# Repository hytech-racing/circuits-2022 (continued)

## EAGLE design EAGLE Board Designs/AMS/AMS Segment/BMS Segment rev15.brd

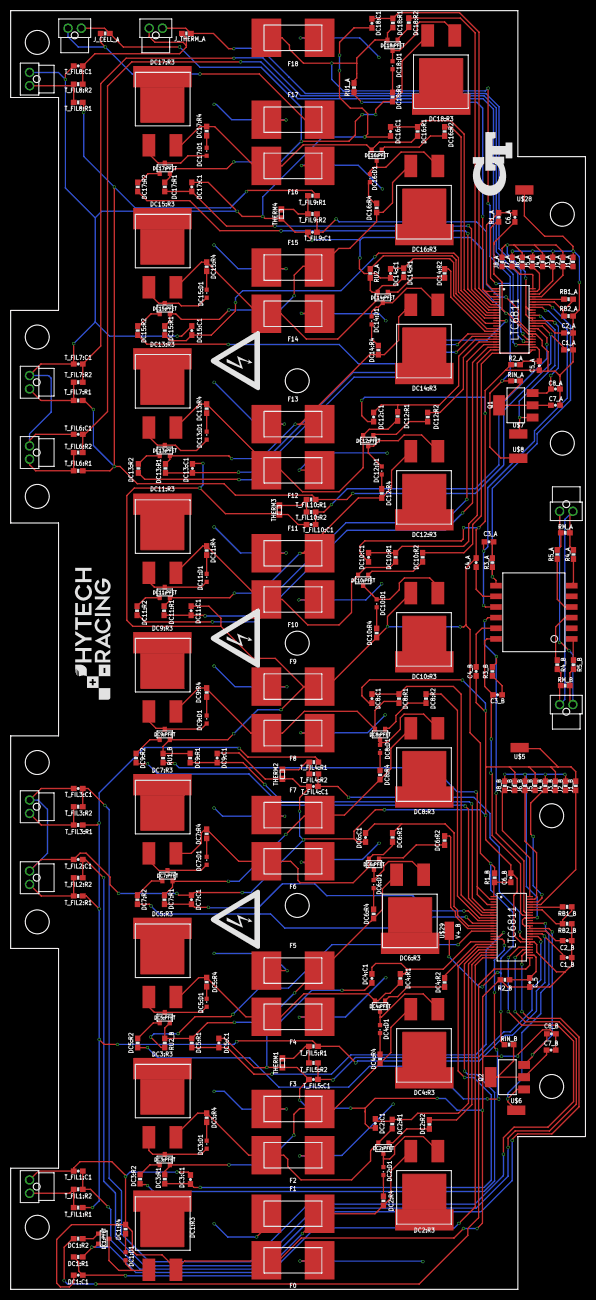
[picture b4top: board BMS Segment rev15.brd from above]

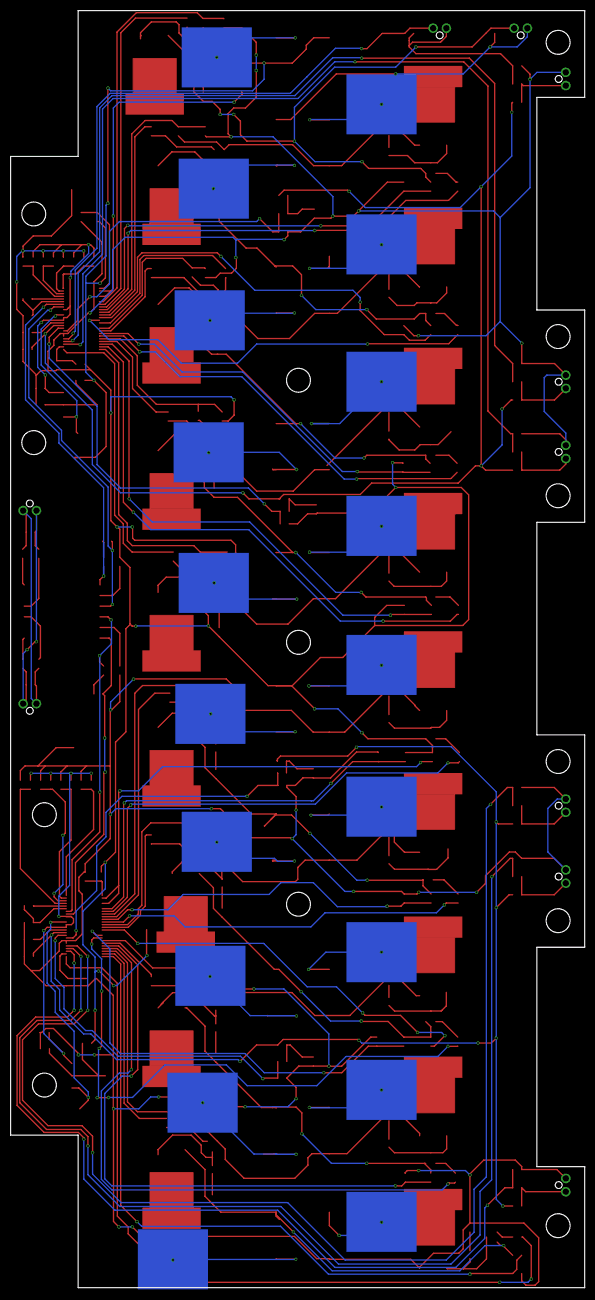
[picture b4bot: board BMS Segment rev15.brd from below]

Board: 2 copper layers, 108.0 x 240.3 mm, 294 parts (19 on the bottom side), 194 nets.

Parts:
AMS_CELL_TEST: AMS_CELL_TEST; NANO-FIT_VERTICAL-2
AMS_THERM_TEST: AMS_THERM_TEST; NANO-FIT_VERTICAL-2
C1_A, C1_B, C2_A, C2_B, C8_A, C8_B: 1uF; 0603-CAP
C3_A, C3_B: 15pF; 0603-CAP
C4_A, C4_B, C5_A: 10nF; 0603-CAP
C6_A, C6_B, C7_A, C7_B: 100nF; 0603-CAP
CELL0, CELL1, CELL2, CELL3, CELL4, CELL5, CELL6, CELL7, CELL8, CELL9, CELL10, CELL11, CELL12, CELL13, CELL14, CELL15, CELL16, CELL17, CELL18: BATTERY_SPRING_KEYSTONE5222; KEYSTONE5222
C_5: 10nF; 0603-CAP
DC1:C1, DC2:C1, DC3:C1, DC4:C1, DC5:C1, DC6:C1, DC7:C1, DC8:C1, DC9:C1, DC10:C1, DC11:C1, DC12:C1, DC13:C1, DC14:C1, DC15:C1, DC16:C1, DC17:C1, DC18:C1: 10nF; 0603-CAP
DC1:D1, DC2:D1, DC3:D1, DC4:D1, DC5:D1, DC6:D1, DC7:D1, DC8:D1, DC9:D1, DC10:D1, DC11:D1, DC12:D1, DC13:D1, DC14:D1, DC15:D1, DC16:D1, DC17:D1, DC18:D1: RED; LED-603
DC1:PFET, DC2:PFET, DC3:PFET, DC4:PFET, DC5:PFET, DC6:PFET, DC7:PFET, DC8:PFET, DC9:PFET, DC10:PFET, DC11:PFET, DC12:PFET, DC13:PFET, DC14:PFET, DC15:PFET, DC16:PFET, DC17:PFET, DC18:PFET: P-CHANNEL_MOSFET_DMP3099L-7; SOT23
DC1:R1, DC2:R1, DC3:R1, DC4:R1, DC5:R1, DC6:R1, DC7:R1, DC8:R1, DC9:R1, DC10:R1, DC11:R1, DC12:R1, DC13:R1, DC14:R1, DC15:R1, DC16:R1, DC17:R1, DC18:R1: 100R; 0603-RES@1
DC1:R2, DC2:R2, DC3:R2, DC4:R2, DC5:R2, DC6:R2, DC7:R2, DC8:R2, DC9:R2, DC10:R2, DC11:R2, DC12:R2, DC13:R2, DC14:R2, DC15:R2, DC16:R2, DC17:R2, DC18:R2: 3K3; 0603-RES@1
DC1:R3, DC2:R3, DC3:R3, DC4:R3, DC5:R3, DC6:R3, DC7:R3, DC8:R3, DC9:R3, DC10:R3, DC11:R3, DC12:R3, DC13:R3, DC14:R3, DC15:R3, DC16:R3, DC17:R3, DC18:R3: RESISTOR_PWR263_; PWR263
DC1:R4, DC2:R4, DC3:R4, DC4:R4, DC5:R4, DC6:R4, DC7:R4, DC8:R4, DC9:R4, DC10:R4, DC11:R4, DC12:R4, DC13:R4, DC14:R4, DC15:R4, DC16:R4, DC17:R4, DC18:R4: 806R; 0603-RES@1
F0, F1, F2, F3, F4, F5, F6, F7, F8, F9, F10, F11, F12, F13, F14, F15, F16, F17, F18: 0001.2704.11; 0885
ISOSPI_A: ISOSPI; NANO-FIT_VERTICAL-2
ISOSPI_B: ISOSPI; NANO-FIT_VERTICAL-2
J1_A, J1_B, J2_A, J2_B, J3_A, J3_B, J4_A, J4_B, J5_A, J5_B, J6_A, J6_B, J7_A, J7_B, J8_A, J8_B: 0R; 0603-RES@1
J_CELL_A: 0R; 0603-RES@1
J_THERM_A: 0R; 0603-RES@1
Q1, Q2: NSV1C201MZ4; SOT223
R1_A, R1_B, R2_A, R2_B: 100R; 0603-RES@1
R3_A, R3_B: 402R; 0603-RES@1
R4_A, R4_B, R5_A, R5_B: 22R; 0603-RES@1
RB1_A, RB1_B: 1K2; 0603-RES@1
RB2_A, RB2_B: 806R; 0603-RES@1
RIN_A: 100R; 0603-RES@1
RIN_B: 100R; 0603-RES@1
RM_A: 100R; 0603-RES@1
RM_B: 100R; 0603-RES@1
RU1_A, RU1_B, RU2_A, RU2_B: 100R; 0603-RES@1
THERM1, THERM2, THERM3, THERM4: 10K; 0603
THERM1_A, THERM1_B, THERM2_A, THERM2_B, THERM3_A, THERM3_B: THERMISTOR; NANO-FIT_VERTICAL-2
TRANSFORMER: HM2102NLT
T_FIL1:C1, T_FIL2:C1, T_FIL3:C1, T_FIL4:C1, T_FIL5:C1, T_FIL6:C1, T_FIL7:C1, T_FIL8:C1, T_FIL9:C1, T_FIL10:C1: 10nF; 0603-CAP
T_FIL1:R1, T_FIL2:R1, T_FIL3:R1, T_FIL4:R1, T_FIL5:R1, T_FIL6:R1, T_FIL7:R1, T_FIL8:R1, T_FIL9:R1, T_FIL10:R1: 10K; 0603-RES@1
T_FIL1:R2, T_FIL2:R2, T_FIL3:R2, T_FIL4:R2, T_FIL5:R2, T_FIL6:R2, T_FIL7:R2, T_FIL8:R2, T_FIL9:R2, T_FIL10:R2: 100R; 0603-RES@1
U1, U2: LTC6811-2; LTC6811
U$1: LOGO_HYTECH_1.0"
U$2: LOGO_GT_0.50"
U$3, U$4, U$20: HV_1.00"
U$5, U$6, U$7, U$8, U$28, U$29: TEST_POINTMICRO_MINIATURE; MICRO_MINIATURE
U$9, U$10, U$11, U$12, U$13, U$14, U$15, U$16, U$17, U$18, U$19, U$26, U$27: M4_MOUNTING
U$21: NUMBER

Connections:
C0_A: C5_A.1, R2_A.2, U1.26
C0_B: C_5.1, R2_B.2, U2.26
C1_A: DC10:C1.1, DC10:R1.2, U1.24
C1_B: DC1:C1.1, DC1:R1.2, U2.24
C2_A: DC11:C1.1, DC11:R1.2, U1.22
C2_B: DC2:C1.1, DC2:R1.2, U2.22
C3_A: DC12:C1.1, DC12:R1.2, U1.20
C3_B: DC3:C1.1, DC3:R1.2, U2.20
C4_A: DC13:C1.1, DC13:R1.2, U1.18
C4_B: DC4:C1.1, DC4:R1.2, U2.18
C5_A: DC14:C1.1, DC14:R1.2, U1.16
C5_B: DC5:C1.1, DC5:R1.2, U2.16
C7_A: DC15:C1.1, DC15:R1.2, U1.12
C7_B: DC6:C1.1, DC6:R1.2, U2.12
C8_A: DC16:C1.1, DC16:R1.2, U1.10
C8_B: DC7:C1.1, DC7:R1.2, U2.10
C9_A: DC17:C1.1, DC17:R1.2, U1.8
C9_B: DC8:C1.1, DC8:R1.2, U2.8
C10_A: DC18:C1.1, DC18:R1.2, U1.6
C10_B: DC9:C1.1, DC9:R1.2, U2.6
CC0: CELL0.1, F0.1
CC1: CELL1.1, F1.1
CC2: CELL2.1, F2.1
CC3: CELL3.1, F3.1
CC4: CELL4.1, F4.1
CC5: CELL5.1, F5.1
CC6: CELL6.1, F6.1
CC7: CELL7.1, F7.1
CC8: CELL8.1, F8.1
CC9: CELL9.1, F9.1
CC10: CELL10.1, F10.1
CC11: CELL11.1, F11.1
CC12: CELL12.1, F12.1
CC13: CELL13.1, F13.1
CC14: CELL14.1, F14.1
CC15: CELL15.1, F15.1
CC16: CELL16.1, F16.1
CC17: CELL17.1, F17.1
CC18: CELL18.1, F18.1
DC1:GATE: DC1:PFET.1, DC1:R2.1
DC1:N$1: DC1:D1.A, DC1:PFET.3, DC1:R3.1
DC1:N$2: DC1:D1.C, DC1:R4.2
DC2:GATE: DC2:PFET.1, DC2:R2.1
DC2:N$1: DC2:D1.A, DC2:PFET.3, DC2:R3.1
DC2:N$2: DC2:D1.C, DC2:R4.2
DC3:GATE: DC3:PFET.1, DC3:R2.1
DC3:N$1: DC3:D1.A, DC3:PFET.3, DC3:R3.1
DC3:N$2: DC3:D1.C, DC3:R4.2
DC4:GATE: DC4:PFET.1, DC4:R2.1
DC4:N$1: DC4:D1.A, DC4:PFET.3, DC4:R3.1
DC4:N$2: DC4:D1.C, DC4:R4.2
DC5:GATE: DC5:PFET.1, DC5:R2.1
DC5:N$1: DC5:D1.A, DC5:PFET.3, DC5:R3.1
DC5:N$2: DC5:D1.C, DC5:R4.2
DC6:GATE: DC6:PFET.1, DC6:R2.1
DC6:N$1: DC6:D1.A, DC6:PFET.3, DC6:R3.1
DC6:N$2: DC6:D1.C, DC6:R4.2
DC7:GATE: DC7:PFET.1, DC7:R2.1
DC7:N$1: DC7:D1.A, DC7:PFET.3, DC7:R3.1
DC7:N$2: DC7:D1.C, DC7:R4.2
DC8:GATE: DC8:PFET.1, DC8:R2.1
DC8:N$1: DC8:D1.A, DC8:PFET.3, DC8:R3.1
DC8:N$2: DC8:D1.C, DC8:R4.2
DC9:GATE: DC9:PFET.1, DC9:R2.1
DC9:N$1: DC9:D1.A, DC9:PFET.3, DC9:R3.1
DC9:N$2: DC9:D1.C, DC9:R4.2
DC10:GATE: DC10:PFET.1, DC10:R2.1
DC10:N$1: DC10:D1.A, DC10:PFET.3, DC10:R3.1
DC10:N$2: DC10:D1.C, DC10:R4.2
DC11:GATE: DC11:PFET.1, DC11:R2.1
DC11:N$1: DC11:D1.A, DC11:PFET.3, DC11:R3.1
DC11:N$2: DC11:D1.C, DC11:R4.2
DC12:GATE: DC12:PFET.1, DC12:R2.1
DC12:N$1: DC12:D1.A, DC12:PFET.3, DC12:R3.1
DC12:N$2: DC12:D1.C, DC12:R4.2
DC13:GATE: DC13:PFET.1, DC13:R2.1
DC13:N$1: DC13:D1.A, DC13:PFET.3, DC13:R3.1
DC13:N$2: DC13:D1.C, DC13:R4.2
DC14:GATE: DC14:PFET.1, DC14:R2.1
DC14:N$1: DC14:D1.A, DC14:PFET.3, DC14:R3.1
DC14:N$2: DC14:D1.C, DC14:R4.2
DC15:GATE: DC15:PFET.1, DC15:R2.1
DC15:N$1: DC15:D1.A, DC15:PFET.3, DC15:R3.1
DC15:N$2: DC15:D1.C, DC15:R4.2
DC16:GATE: DC16:PFET.1, DC16:R2.1
DC16:N$1: DC16:D1.A, DC16:PFET.3, DC16:R3.1
DC16:N$2: DC16:D1.C, DC16:R4.2
DC17:GATE: DC17:PFET.1, DC17:R2.1
DC17:N$1: DC17:D1.A, DC17:PFET.3, DC17:R3.1
DC17:N$2: DC17:D1.C, DC17:R4.2
DC18:GATE: DC18:PFET.1, DC18:R2.1
DC18:N$1: DC18:D1.A, DC18:PFET.3, DC18:R3.1
DC18:N$2: DC18:D1.C, DC18:R4.2
DRIVE_A: Q1.1, U1.38, U$7.1
DRIVE_B: Q2.1, U2.38, U$6.1
GPIO1_A: T_FIL6:C1.1, T_FIL6:R2.1, U1.27
GPIO1_B: T_FIL1:C1.1, T_FIL1:R2.1, U2.27
GPIO2_A: T_FIL7:C1.1, T_FIL7:R2.1, U1.28
GPIO2_B: T_FIL2:C1.1, T_FIL2:R2.1, U2.28
GPIO3_A_POST: AMS_THERM_TEST.P$2, J_THERM_A.1, U1.29
GPIO3_A_PRE: AMS_THERM_TEST.P$1, J_THERM_A.2, T_FIL8:C1.1, T_FIL8:R2.1
GPIO3_B: T_FIL3:C1.1, T_FIL3:R2.1, U2.29
GPIO4_A: T_FIL9:C1.1, T_FIL9:R2.1, U1.32
GPIO4_B: T_FIL4:C1.1, T_FIL4:R2.1, U2.32
GPIO5_A: T_FIL10:C1.1, T_FIL10:R2.1, U1.33
GPIO5_B: T_FIL5:C1.1, T_FIL5:R2.1, U2.33
IM_A: C3_A.2, TRANSFORMER.P$9, U1.41
IM_B: C3_B.2, TRANSFORMER.P$12, U2.41
IP_A: R3_A.1, TRANSFORMER.P$7, U1.42
IP_B: R3_B.1, TRANSFORMER.P$10, U2.42
ISOSPI-M: ISOSPI_A.P$2, ISOSPI_B.P$2, R5_A.2, R5_B.2, RM_A.2, RM_B.2
ISOSPI-P: ISOSPI_A.P$1, ISOSPI_B.P$1, R4_A.2, R4_B.2, RM_A.1, RM_B.1
unnamed: C4_B.1, TRANSFORMER.P$11
unnamed: RB1_B.2, U2.44
unnamed: THERM1_B.P$1, T_FIL1:R1.2, T_FIL1:R2.2
unnamed: RB1_B.1, RB2_B.2, U2.43
unnamed: R4_B.1, TRANSFORMER.P$3
unnamed: RB1_A.2, U1.44
unnamed: R5_B.1, TRANSFORMER.P$1
unnamed: J7_B.1, J8_B.1, U2.48
unnamed: J5_B.1, J6_B.1, U2.47
unnamed: C3_B.1, R3_B.2
unnamed: J3_B.1, J4_B.1, U2.46
unnamed: J1_B.1, J2_B.1, U2.45
unnamed: THERM1.2, T_FIL5:R1.2, T_FIL5:R2.2
unnamed: THERM2_B.P$1, T_FIL2:R1.2, T_FIL2:R2.2
unnamed: THERM2.2, T_FIL4:R1.2, T_FIL4:R2.2
unnamed: RB1_A.1, RB2_A.2, U1.43
unnamed: C4_A.1, TRANSFORMER.P$8
unnamed: R4_A.1, TRANSFORMER.P$6
unnamed: R5_A.1, TRANSFORMER.P$4
unnamed: C3_A.1, R3_A.2
unnamed: THERM3_B.P$1, T_FIL3:R1.2, T_FIL3:R2.2
unnamed: J7_A.1, J8_A.1, U1.48
unnamed: J5_A.1, J6_A.1, U1.47
unnamed: J3_A.1, J4_A.1, U1.46
unnamed: J1_A.1, J2_A.1, U1.45
unnamed: THERM4.2, T_FIL9:R1.2, T_FIL9:R2.2
unnamed: THERM3_A.P$1, T_FIL8:R1.2, T_FIL8:R2.2
unnamed: THERM3.2, T_FIL10:R1.2, T_FIL10:R2.2
unnamed: THERM2_A.P$1, T_FIL7:R1.2, T_FIL7:R2.2
unnamed: THERM1_A.P$1, T_FIL6:R1.2, T_FIL6:R2.2
S1_A: DC10:R2.2, U1.25
S1_B: DC1:R2.2, U2.25
S2_A: DC11:R2.2, U1.23
S2_B: DC2:R2.2, U2.23
S3_A: DC12:R2.2, U1.21
S3_B: DC3:R2.2, U2.21
S4_A: DC13:R2.2, U1.19
S4_B: DC4:R2.2, U2.19
S5_A: DC14:R2.2, U1.17
S5_B: DC5:R2.2, U2.17
S7_A: DC15:R2.2, U1.13
S7_B: DC6:R2.2, U2.13
S8_A: DC16:R2.2, U1.11
S8_B: DC7:R2.2, U2.11
S9_A: DC17:R2.2, U1.9
S9_B: DC8:R2.2, U2.9
S10_A: DC18:R2.2, U1.7
S10_B: DC9:R2.2, U2.7
SENSE1: DC1:PFET.2, DC1:R1.1, DC2:R3.2, DC2:R4.1, F1.2
SENSE2: DC2:PFET.2, DC2:R1.1, DC3:R3.2, DC3:R4.1, F2.2
SENSE3: DC3:PFET.2, DC3:R1.1, DC4:R3.2, DC4:R4.1, F3.2
SENSE4: DC4:PFET.2, DC4:R1.1, DC5:R3.2, DC5:R4.1, F4.2
SENSE5: DC5:PFET.2, DC5:R1.1, DC6:R3.2, DC6:R4.1, F5.2, RU2_B.1
SENSE6: DC6:PFET.2, DC6:R1.1, DC7:R3.2, DC7:R4.1, F6.2
SENSE7: DC7:PFET.2, DC7:R1.1, DC8:R3.2, DC8:R4.1, F7.2
SENSE8: DC8:PFET.2, DC8:R1.1, DC9:R3.2, DC9:R4.1, F8.2
SENSE10: DC10:PFET.2, DC10:R1.1, DC11:R3.2, DC11:R4.1, F10.2
SENSE11: DC11:PFET.2, DC11:R1.1, DC12:R3.2, DC12:R4.1, F11.2
SENSE12: DC12:PFET.2, DC12:R1.1, DC13:R3.2, DC13:R4.1, F12.2
SENSE13: DC13:PFET.2, DC13:R1.1, DC14:R3.2, DC14:R4.1, F13.2
SENSE14: DC14:PFET.2, DC14:R1.1, DC15:R3.2, DC15:R4.1, F14.2, RU2_A.1
SENSE15: DC15:PFET.2, DC15:R1.1, DC16:R3.2, DC16:R4.1, F15.2
SENSE16: DC16:PFET.2, DC16:R1.1, DC17:R3.2, DC17:R4.1, F16.2
SENSE17_POST: AMS_CELL_TEST.P$2, DC17:PFET.2, DC17:R1.1, DC18:R3.2, DC18:R4.1, J_CELL_A.2
SENSE17_PRE: AMS_CELL_TEST.P$1, F17.2, J_CELL_A.1
SENSE18: DC18:PFET.2, DC18:R1.1, F18.2, R1_A.1, RIN_A.1, RU1_A.1, U$8.1
UNUSED1_A: RU1_A.2, U1.2, U1.4
UNUSED1_B: RU1_B.2, U2.2, U2.4
UNUSED2_A: RU2_A.2, U1.14
UNUSED2_B: RU2_B.2, U2.14
V+_A: C6_A.1, R1_A.2, U1.1
V+_B: C6_B.1, R1_B.2, U2.1
V-_A: C1_A.2, C2_A.2, C4_A.2, C5_A.2, C6_A.2, C7_A.2, C8_A.2, DC9:PFET.2, DC9:R1.1, DC10:C1.2, DC10:R3.2, DC10:R4.1, DC11:C1.2, DC12:C1.2, DC13:C1.2, DC14:C1.2, DC15:C1.2, DC16:C1.2, DC17:C1.2, DC18:C1.2, F9.2, J1_A.2, J3_A.2, J5_A.2, J7_A.2, R1_B.1, R2_A.1, RB2_A.1, RIN_B.1, RU1_B.1, THERM1_A.P$2, THERM2_A.P$2, THERM3.1, THERM3_A.P$2, THERM4.1, T_FIL6:C1.2, T_FIL7:C1.2, T_FIL8:C1.2, T_FIL9:C1.2, T_FIL10:C1.2, U1.30, U1.31, U$28.1, U$29.1
V-_B: C1_B.2, C2_B.2, C4_B.2, C6_B.2, C7_B.2, C8_B.2, C_5.2, DC1:C1.2, DC1:R3.2, DC1:R4.1, DC2:C1.2, DC3:C1.2, DC4:C1.2, DC5:C1.2, DC6:C1.2, DC7:C1.2, DC8:C1.2, DC9:C1.2, F0.2, J1_B.2, J3_B.2, J5_B.2, J7_B.2, R2_B.1, RB2_B.1, THERM1.1, THERM1_B.P$2, THERM2.1, THERM2_B.P$2, THERM3_B.P$2, T_FIL1:C1.2, T_FIL2:C1.2, T_FIL3:C1.2, T_FIL4:C1.2, T_FIL5:C1.2, U2.30, U2.31, U$5.1
VIN_A: C7_A.1, Q1.2, Q1.4, RIN_A.2
VIN_B: C7_B.1, Q2.2, Q2.4, RIN_B.2
VREF1_A: C2_A.1, U1.35
VREF1_B: C2_B.1, U2.35
VREF2_A: C1_A.1, T_FIL6:R1.1, T_FIL7:R1.1, T_FIL8:R1.1, T_FIL9:R1.1, T_FIL10:R1.1, U1.34
VREF2_B: C1_B.1, T_FIL1:R1.1, T_FIL2:R1.1, T_FIL3:R1.1, T_FIL4:R1.1, T_FIL5:R1.1, U2.34
VREG_A: C8_A.1, J2_A.2, J4_A.2, J6_A.2, J8_A.2, Q1.3, U1.36, U1.37, U1.40
VREG_B: C8_B.1, J2_B.2, J4_B.2, J6_B.2, J8_B.2, Q2.3, U2.36, U2.37, U2.40

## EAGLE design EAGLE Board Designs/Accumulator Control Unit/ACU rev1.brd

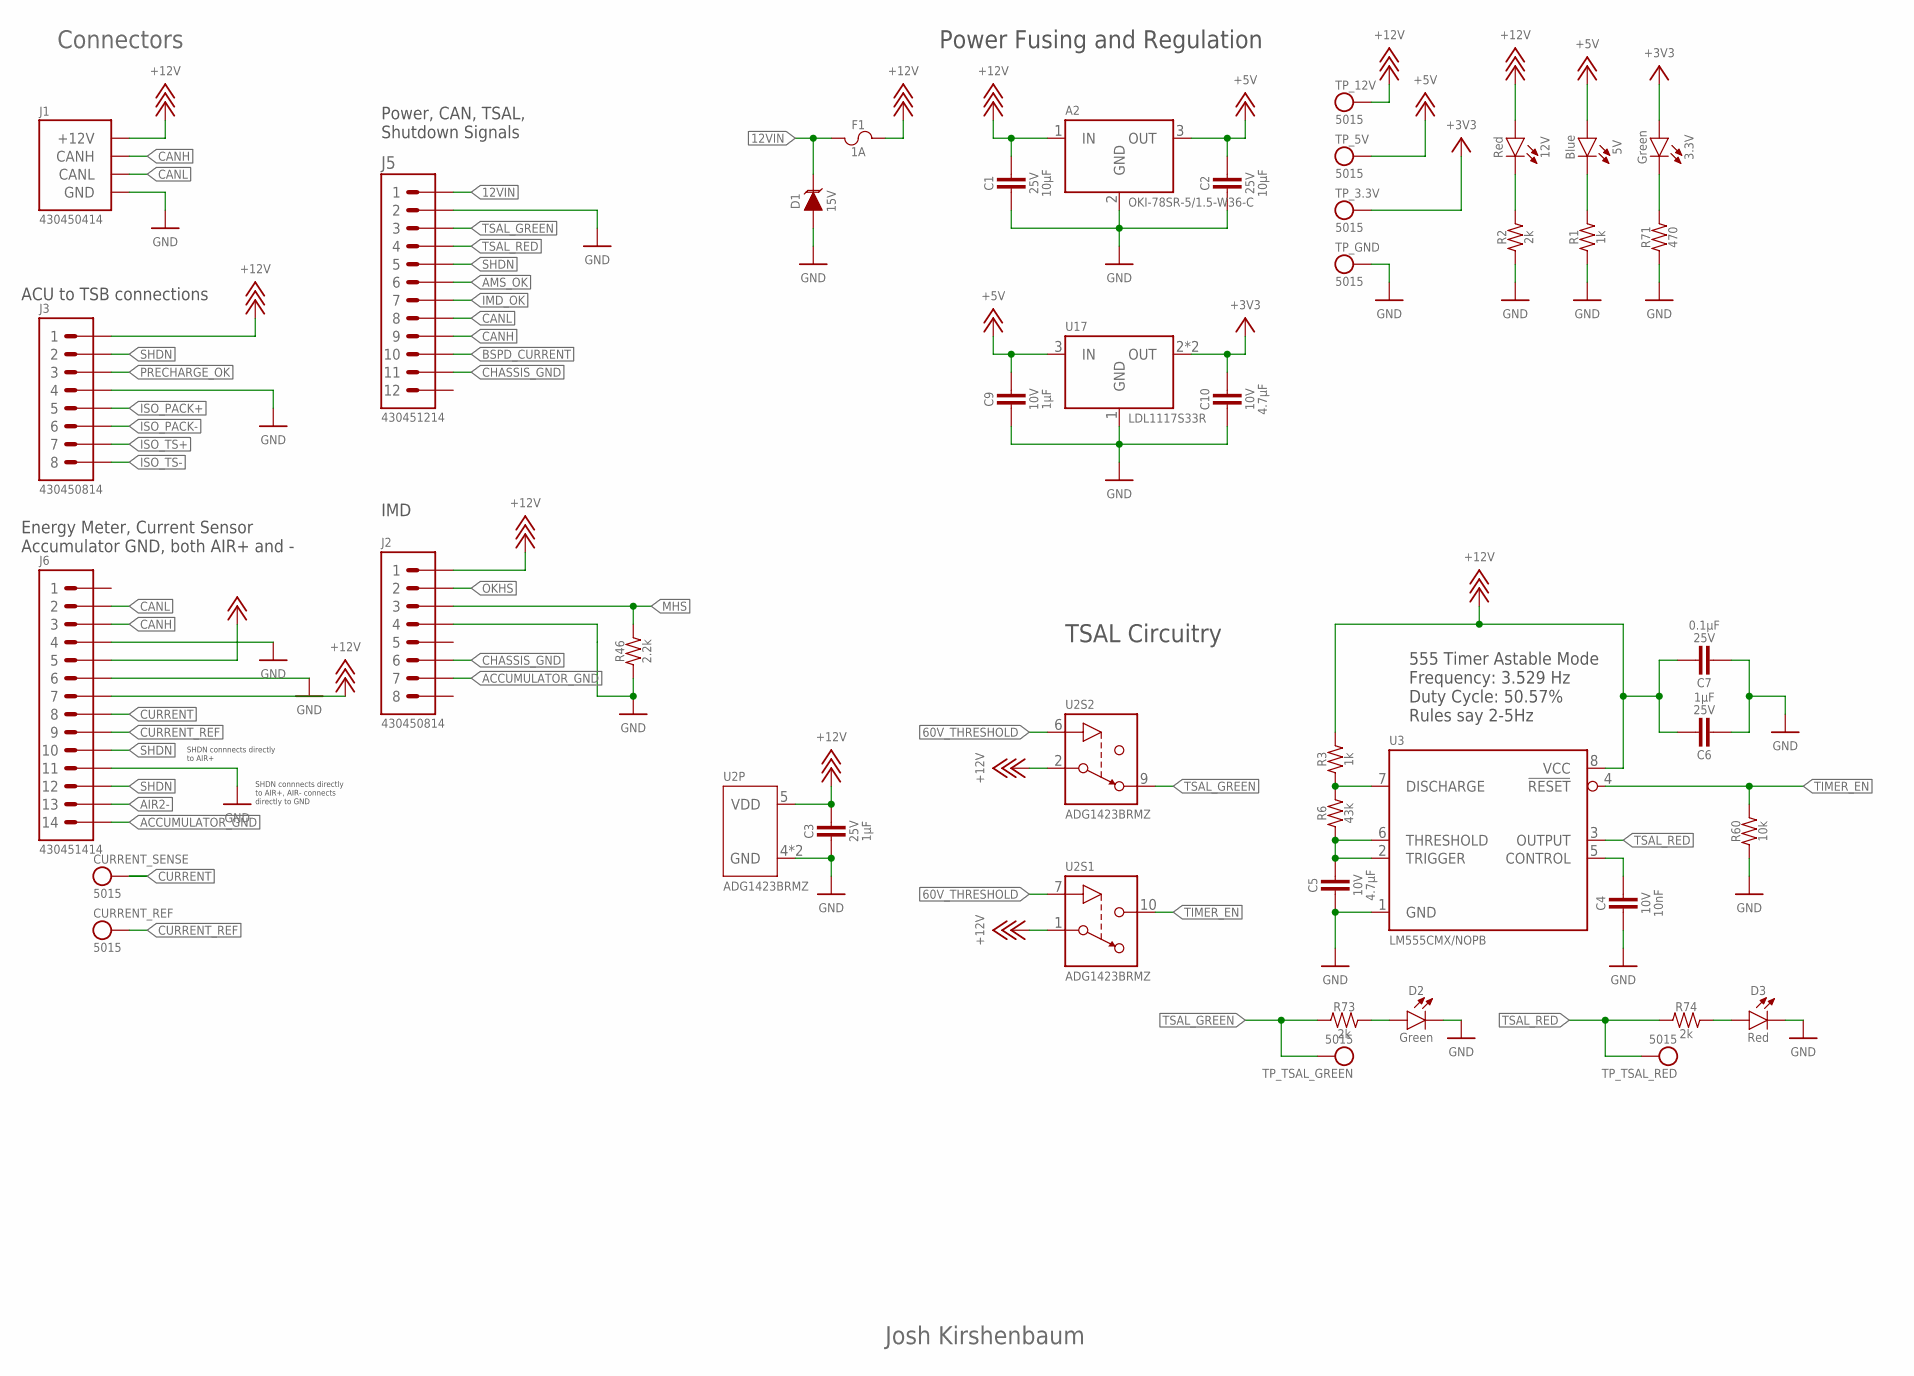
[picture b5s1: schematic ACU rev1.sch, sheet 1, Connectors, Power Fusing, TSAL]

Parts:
3.3V: LED_0603_GREEN; 0603-LED
5V: LED_0603_BLUE; 0603-LED
12V: LED_0603_RED; 0603-LED
A2: VOLTAGE_REGULATOR_MODULE_OKI-78SR_5V; OKI-78SR
C1, C2: CAPACITOR_0603_25V_10UF; 0603-CAP
C3, C6: CAPACITOR_0603_25V_1UF; 0603-CAP
C4: CAPACITOR_0603_10V_10NF; 0603-CAP
C5, C10: CAPACITOR_0603_10V_4.7UF; 0603-CAP
C7: CAPACITOR_0603_25V_0.1UF; 0603-CAP
C9: CAPACITOR_0603_10V_1UF; 0603-CAP
CURRENT_REF: TEST_POINT; MICRO_MINIATURE
CURRENT_SENSE: TEST_POINT; MICRO_MINIATURE
D1: TVS_15V; SOT-23
D2: LED_0603_GREEN; 0603-LED
D3: LED_0603_RED; 0603-LED
F1: FUSE_MINI-BLADE_1A; MINI-BLADE_FUSE_HOLDER
J1: CONNECTOR-CAN_MF_T_V_; MOLEX_MICROFIT_PTH_VERTICAL_04_DUAL
J2, J3: CONNECTOR-8_MF_T_V_; MOLEX_MICROFIT_PTH_VERTICAL_08_DUAL
J5: CONNECTOR-12_MF_T_V_; MOLEX_MICROFIT_PTH_VERTICAL_12_DUAL
J6: CONNECTOR-14_MF_T_V_; MOLEX_MICROFIT_PTH_VERTICAL_14_DUAL
R1, R3: RESISTOR_0603_1K; 0603-RES
R2, R73, R74: RESISTOR_0603_2K; 0603-RES
R6: RESISTOR_0603_43K; 0603-RES
R46: RESISTOR_0603_2.2K; 0603-RES
R60: RESISTOR_0603_10K; 0603-RES
R71: RESISTOR_0603_470; 0603-RES
TP_3.3V, TP_5V, TP_12V: TEST_POINT; MICRO_MINIATURE
TP_GND: TEST_POINT; MICRO_MINIATURE
TP_TSAL_GREEN: TEST_POINT; MICRO_MINIATURE
TP_TSAL_RED: TEST_POINT; MICRO_MINIATURE
U2: ADG1423; MSOP-10
U3: LM555; SOIC-08(NARROW,0.15")
U17: VOLTAGE_REGULATOR_SOT223_3.3V; SOT223

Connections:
12VIN: D1.3 (C), F1.L1 (1), F1.L2 (1), J5.1
60V_THRESHOLD: U2.6 (IN), U2.7 (IN); also elsewhere on the board
+3V3: 3.3V.2 (A), C10.1, TP_3.3V.1, U17.2 (OUT), U17.4 (OUT); also elsewhere on the board
+5V: 5V.2 (A), A2.3 (OUT), C2.1, C9.1, J6.5, TP_5V.1, U17.3 (IN); also elsewhere on the board
+12V: 12V.2 (A), A2.1 (IN), C1.1, C3.1, C6.1, C7.1, F1.R1 (2), F1.R2 (2), J1.1 (+12V), J2.1, J3.1, J6.7, R3.2, TP_12V.1, U2.1 (S), U2.2 (S), U2.5 (VDD), U3.8 (VCC); also elsewhere on the board
ACCUMULATOR_GND: J2.7, J6.14
AIR2-: J6.13; also elsewhere on the board
AMS_OK: J5.6; also elsewhere on the board
BSPD_CURRENT: J5.10; also elsewhere on the board
CANH: J1.4 (CANH), J5.9, J6.3; also elsewhere on the board
CANL: J1.3 (CANL), J5.8, J6.2; also elsewhere on the board
CHASSIS_GND: J2.6, J5.11
CURRENT: CURRENT_SENSE.1, J6.8; also elsewhere on the board
CURRENT_REF: CURRENT_REF.1, J6.9; also elsewhere on the board
GND: A2.2 (GND), C1.2, C2.2, C3.2, C4.2, C5.2, C6.2, C7.2, C9.2, C10.2, D1.1 (A), D2.1 (C), D3.1 (C), J1.2 (GND), J2.4, J3.4, J5.2, J6.4, J6.6, J6.11, R1.1, R2.1, R46.1, R60.1, R71.1, TP_GND.1, U2.4 (GND), U2.8 (GND), U3.1 (GND), U17.1 (GND); also elsewhere on the board
IMD_OK: J5.7; also elsewhere on the board
ISO_PACK+: J3.5; also elsewhere on the board
ISO_PACK-: J3.6; also elsewhere on the board
ISO_TS+: J3.7; also elsewhere on the board
ISO_TS-: J3.8; also elsewhere on the board
MHS: J2.3, R46.2; also elsewhere on the board
unnamed: 3.3V.1 (C), R71.2
unnamed: 5V.1 (C), R1.2
unnamed: C5.1, R6.1, U3.2 (TRIGGER), U3.6 (THRESHOLD)
unnamed: C4.1, U3.5 (CONTROL)
unnamed: R3.1, R6.2, U3.7 (DISCHARGE)
unnamed: 12V.1 (C), R2.2
unnamed: D2.2 (A), R73.2
unnamed: D3.2 (A), R74.2
OKHS: J2.2; also elsewhere on the board
PRECHARGE_OK: J3.3; also elsewhere on the board
SHDN: J3.2, J5.5, J6.10, J6.12
TIMER_EN: R60.2, U2.10 (D), U3.4 (!RESET)
TSAL_GREEN: J5.3, R73.1, TP_TSAL_GREEN.1, U2.9 (D)
TSAL_RED: J5.4, R74.1, TP_TSAL_RED.1, U3.3 (OUTPUT)

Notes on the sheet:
Josh Kirshenbaum
Connectors
ACU to TSB connections
Power, CAN, TSAL, Shutdown Signals
Power Fusing and Regulation
SHDN connnects directly to AIR+, AIR- connects directly to GND
TSAL Circuitry
555 Timer Astable Mode Frequency: 3.529 Hz Duty Cycle: 50.57% Rules say 2-5Hz
SHDN connnects directly to AIR+
Energy Meter, Current Sensor Accumulator GND, both AIR+ and -
IMD

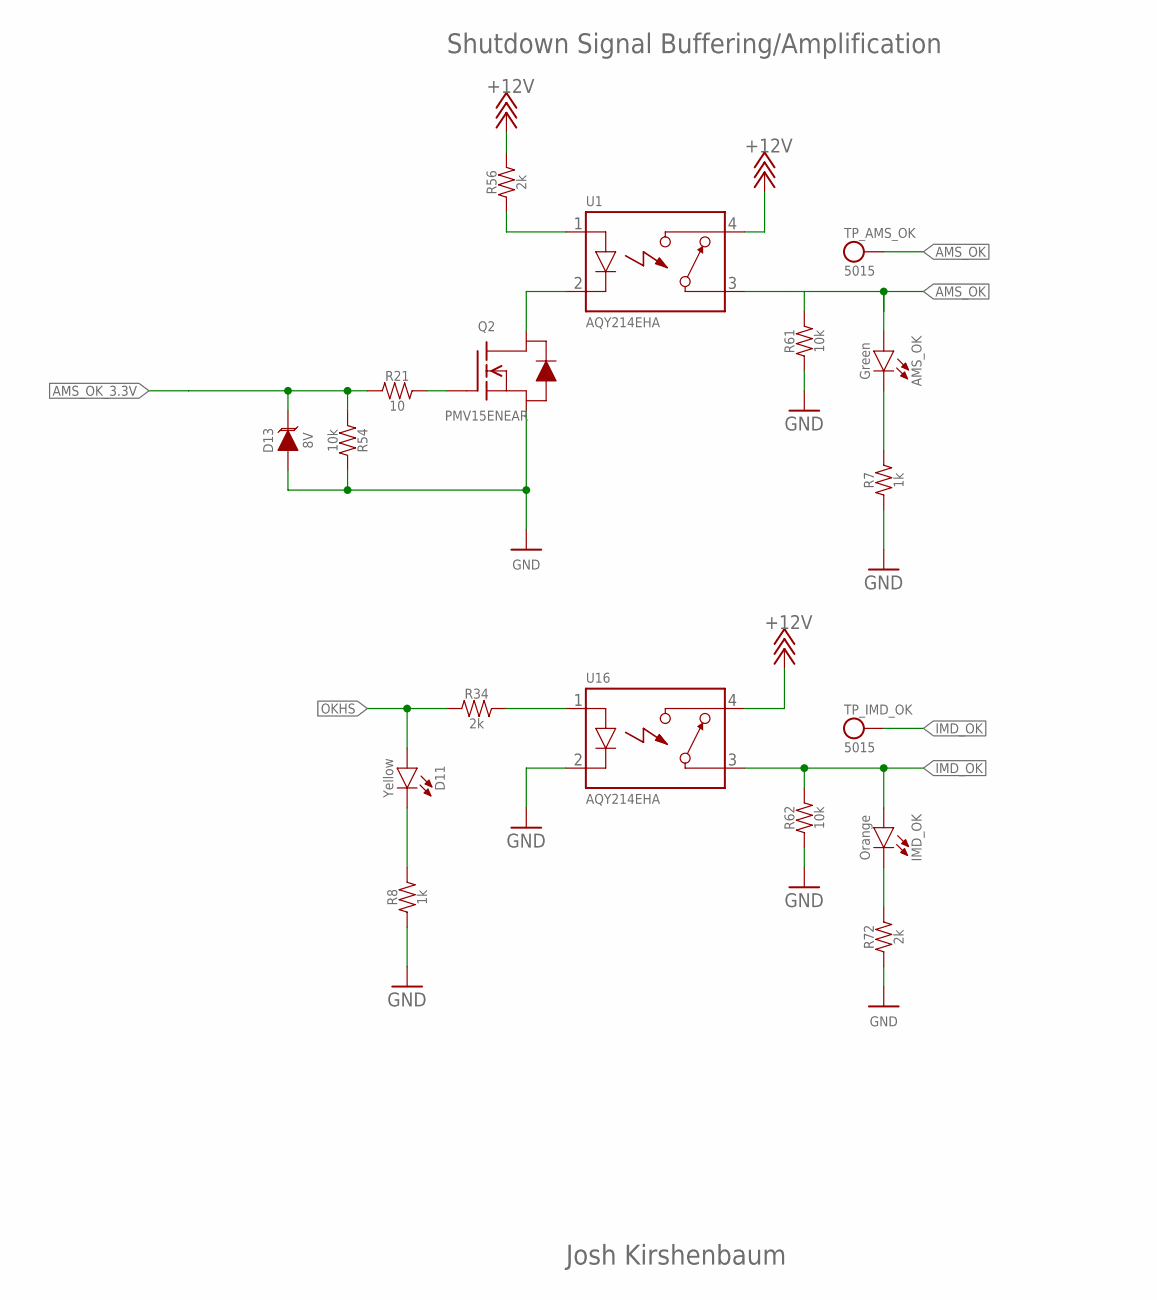
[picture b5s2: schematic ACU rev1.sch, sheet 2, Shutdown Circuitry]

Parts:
AMS_OK: LED_0603_GREEN; 0603-LED
D11: LED_0603_YELLOW; 0603-LED
D13: TVS_8V; SOT-23
IMD_OK: LED_0603_ORANGE; 0603-LED
Q2: TRANSISTOR_N_MOS__PMV15ENEA; SOT-23
R7, R8: RESISTOR_0603_1K; 0603-RES
R21: RESISTOR_0603_10; 0603-RES
R34, R56, R72: RESISTOR_0603_2K; 0603-RES
R54, R61, R62: RESISTOR_0603_10K; 0603-RES
TP_AMS_OK: TEST_POINT; MICRO_MINIATURE
TP_IMD_OK: TEST_POINT; MICRO_MINIATURE
U1, U16: RELAY_SOLIDSTATE_NO; DIP-4

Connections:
+12V: R56.2, U1.4 (CONTACT2), U16.4 (CONTACT2); also elsewhere on the board
AMS_OK: AMS_OK.2 (A), R61.2, TP_AMS_OK.1, U1.3 (CONTACT1); also elsewhere on the board
AMS_OK_3.3V: D13.3 (C), R21.1, R54.1; also elsewhere on the board
GND: D13.1 (A), Q2.2 (S), R7.1, R8.1, R54.2, R61.1, R62.1, R72.1, U16.2 (CONTROL-); also elsewhere on the board
IMD_OK: IMD_OK.2 (A), R62.2, TP_IMD_OK.1, U16.3 (CONTACT1); also elsewhere on the board
unnamed: R34.2, U16.1 (CONTROL+)
unnamed: D11.1 (C), R8.2
unnamed: R56.1, U1.1 (CONTROL+)
unnamed: AMS_OK.1 (C), R7.2
unnamed: Q2.3 (D), U1.2 (CONTROL-)
unnamed: IMD_OK.1 (C), R72.2
unnamed: Q2.1 (G), R21.2
OKHS: D11.2 (A), R34.1; also elsewhere on the board

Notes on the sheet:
Josh Kirshenbaum
Shutdown Signal Buffering/Amplification

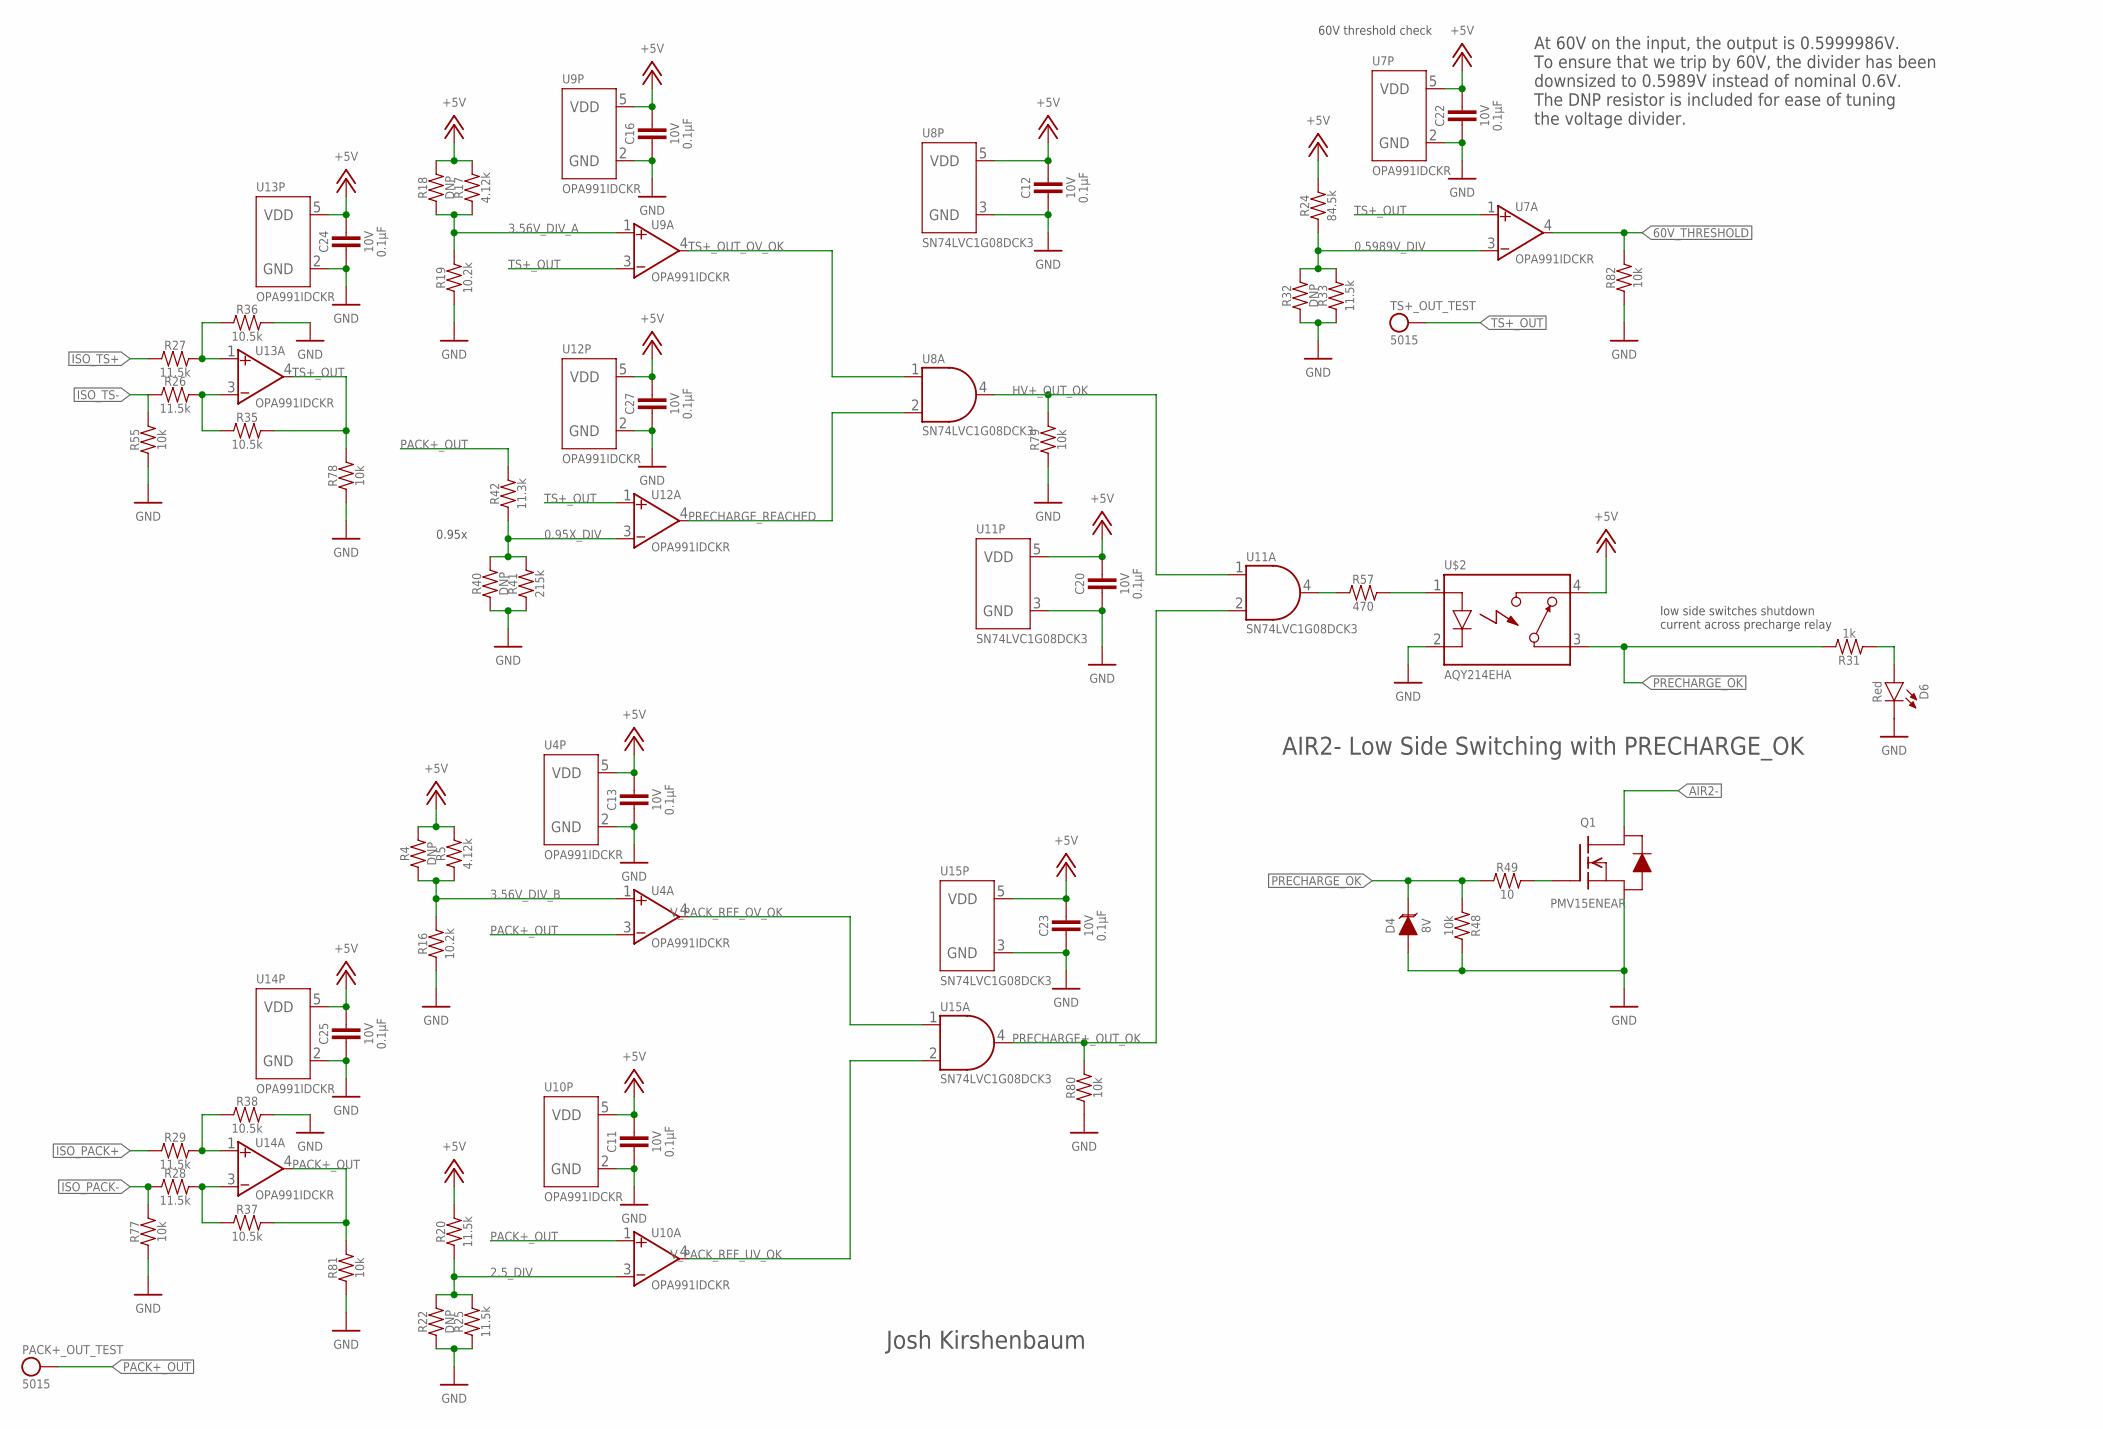
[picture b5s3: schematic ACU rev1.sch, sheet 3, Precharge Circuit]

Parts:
C11, C12, C13, C16, C20, C22, C23, C24, C25, C27: CAPACITOR_0603_10V_0.1UF; 0603-CAP
D4: TVS_8V; SOT-23
D6: LED_0603_RED; 0603-LED
PACK+_OUT_TEST: TEST_POINT; MICRO_MINIATURE
Q1: TRANSISTOR_N_MOS__PMV15ENEA; SOT-23
R4, R18, R22, R32, R40: RESISTOR_0603_DNP; 0603-RES
R5, R17: RESISTOR_0603_4.12K; 0603-RES
R16, R19: RESISTOR_0603_10.2K; 0603-RES
R20, R25, R26, R27, R28, R29, R33: RESISTOR_0603_11.5K; 0603-RES
R24: RESISTOR_0603_84.5K; 0603-RES
R31: RESISTOR_0603_1K; 0603-RES
R35, R36, R37, R38: RESISTOR_0603_10.5K; 0603-RES
R41: RESISTOR_0603_215K; 0603-RES
R42: RESISTOR_0603_11.3K; 0603-RES
R48, R55, R77, R78, R79, R80, R81, R82: RESISTOR_0603_10K; 0603-RES
R49: RESISTOR_0603_10; 0603-RES
R57: RESISTOR_0603_470; 0603-RES
TS+_OUT_TEST: TEST_POINT; MICRO_MINIATURE
U4, U7, U9, U10, U12, U13, U14: OPAMP_1_CHANNEL_OPA991; SC-70-5
U8, U11, U15: LOGICGATE_AND_DCK3; SC-70-5
U$2: RELAY_SOLIDSTATE_NO; DIP-4

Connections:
0.95X_DIV: R40.2, R41.2, R42.1, U12.3 (VIN-)
0.5989V_DIV: R24.1, R32.2, R33.2, U7.3 (VIN-)
2.5_DIV: R20.1, R22.2, R25.2, U10.3 (VIN-)
3.56V_DIV_A: R17.1, R18.1, R19.2, U9.1 (VIN+)
3.56V_DIV_B: R4.1, R5.1, R16.2, U4.1 (VIN+)
60V_THRESHOLD: R82.2, U7.4 (VOUT); also elsewhere on the board
+5V: C11.1, C12.1, C13.1, C16.1, C20.1, C22.1, C23.1, C24.1, C25.1, C27.1, R4.2, R5.2, R17.2, R18.2, R20.2, R24.2, U4.5 (VDD), U7.5 (VDD), U8.5 (VDD), U9.5 (VDD), U10.5 (VDD), U11.5 (VDD), U12.5 (VDD), U13.5 (VDD), U14.5 (VDD), U15.5 (VDD), U$2.4 (CONTACT2); also elsewhere on the board
AIR2-: Q1.3 (D); also elsewhere on the board
GND: C11.2, C12.2, C13.2, C16.2, C20.2, C22.2, C23.2, C24.2, C25.2, C27.2, D4.1 (A), D6.1 (C), Q1.2 (S), R16.1, R19.1, R22.1, R25.1, R32.1, R33.1, R36.2, R38.2, R40.1, R41.1, R48.2, R55.1, R77.1, R78.1, R79.1, R80.1, R81.1, R82.1, U4.2 (GND), U7.2 (GND), U8.3 (GND), U9.2 (GND), U10.2 (GND), U11.3 (GND), U12.2 (GND), U13.2 (GND), U14.2 (GND), U15.3 (GND), U$2.2 (CONTROL-); also elsewhere on the board
HV+_OUT_OK: R79.2, U8.4 (OUT), U11.1 (IN1)
ISO_PACK+: R29.1; also elsewhere on the board
ISO_PACK-: R28.1, R77.2; also elsewhere on the board
ISO_TS+: R27.1; also elsewhere on the board
ISO_TS-: R26.1, R55.2; also elsewhere on the board
unnamed: D6.2 (A), R31.1
unnamed: Q1.1 (G), R49.2
unnamed: R27.2, R36.1, U13.1 (VIN+)
unnamed: R26.2, R35.1, U13.3 (VIN-)
unnamed: R29.2, R38.1, U14.1 (VIN+)
unnamed: R28.2, R37.1, U14.3 (VIN-)
unnamed: R57.1, U11.4 (OUT)
unnamed: R57.2, U$2.1 (CONTROL+)
PACK+_OUT: PACK+_OUT_TEST.1, R37.2, R42.2, R81.2, U4.3 (VIN-), U10.1 (VIN+), U14.4 (VOUT); also elsewhere on the board
PRECHARGE+_OUT_OK: R80.2, U11.2 (IN2), U15.4 (OUT)
PRECHARGE_OK: D4.3 (C), R31.2, R48.1, R49.1, U$2.3 (CONTACT1); also elsewhere on the board
PRECHARGE_REACHED: U8.2 (IN2), U12.4 (VOUT); also elsewhere on the board
TS+_OUT: R35.2, R78.2, TS+_OUT_TEST.1, U7.1 (VIN+), U9.3 (VIN-), U12.1 (VIN+), U13.4 (VOUT); also elsewhere on the board
TS+_OUT_OV_OK: U8.1 (IN1), U9.4 (VOUT); also elsewhere on the board
V_PACK_REF_OV_OK: U4.4 (VOUT), U15.1 (IN1); also elsewhere on the board
V_PACK_REF_UV_OK: U10.4 (VOUT), U15.2 (IN2); also elsewhere on the board

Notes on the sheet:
60V threshold check
At 60V on the input, the output is 0.5999986V. To ensure that we trip by 60V, the divider has been downsized to 0.5989V instead of nominal 0.6V. The DNP resistor is included for ease of tuning the voltage divider.
0.95x
low side switches shutdown current across precharge relay
Josh Kirshenbaum
AIR2- Low Side Switching with PRECHARGE_OK
